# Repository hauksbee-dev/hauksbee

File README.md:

# Hauksbee

**Your design files already contain a running system, with Hauksbee you execute it.**

Hand Hauksbee the artifacts you already produce: the layout, schematic, fab archive, BOM and placement data, fitted variant, compiled firmware, or even the faulty and fixed revisions in a git history. It reconstructs the circuit the copper implements, binds device models, solves it, and boots firmware against the solved board. Findings arrive with the exact evidence that caused them.

A design-rule checker checks geometry against rules. A schematic simulator executes the circuit it was given. Hauksbee's different job is to execute and cross-check the evidence that will become the product: native design files, manufacturing output, assembled-part identity, and firmware.

**New here?** Start with [START_HERE](docs/START_HERE.md). The authoritative scope and backend matrix live in [CAPABILITIES](docs/about/CAPABILITIES.md) and [LIMITATIONS](docs/about/LIMITATIONS.md).

## Get Hauksbee

No binary release is published yet, so build from source. From a checkout of
this repository on macOS/Linux:

```bash
scripts/install-sims.sh --check   # reports which simulator backends are missing
scripts/install.sh
```

`scripts/install.sh` checks the Rust, Bun, clang/libclang, and libsimavr
prerequisites, builds the default shape, and installs `hauksbee`, `hauksbee-ci`,
and `hauksbee-mcp`; external simulators use `scripts/install-sims.sh`. Windows
x64 uses the permissive build documented in
[START_HERE](docs/START_HERE.md#install-and-first-run). Signing, notarisation,
and artifact provenance are release gates; see
[release and licensing](docs/about/release-and-licensing.md).

Once a release is published, the installers below fetch the latest release and
check each asset against the `.sha256` sidecar published beside it. Until then
they exit with an error. Hauksbee is pre-1.0, so you may prefer to pin a tag:
add `-s -- --version vX.Y.Z` after `bash` (PowerShell: download the script and
pass `-Version vX.Y.Z`).

```bash
curl -fsSL https://raw.githubusercontent.com/hauksbee-dev/hauksbee/main/scripts/get-hauksbee.sh | bash
```

Windows (PowerShell):

```powershell
irm https://raw.githubusercontent.com/hauksbee-dev/hauksbee/main/scripts/get-hauksbee.ps1 | iex
```

Once a release exists, `Hauksbee.app` will also be on the
[release page](https://github.com/hauksbee-dev/hauksbee/releases/latest); a
macOS app is published only after its same-source signing and notarisation
gates pass. Ordinary analysis is local. The optional datasheet drafting sends
the datasheet's text to the LLM backend you chose, only after an explicit
consent notice (see
[choosing a backend](docs/models/MODELS.md#choosing-a-backend)); nothing is
ever attached to an issue automatically.

Once the public GHCR package is published, CI images are available as `:slim`
(static checks + AVR co-sim) and `:full` (adds Renode, Espressif QEMU, and
autorouting). Use immutable version/digest references, not floating tags. See
[DOCKER](docs/ci/DOCKER.md).

## Five kinds of evidence, one engine

### Board evidence

Native KiCad, Eagle, Altium, EasyEDA, IPC-2581, ODB++, and schematic-only inputs become one electrical intermediate representation. Static checks, model binding, solver construction, and firmware coupling all consume that same representation rather than separate hand-translated, often idealised diagrams.

### Fab evidence

Gerber, drill, job metadata, and IPC-D-356 can reconstruct what the factory was asked to make. The current closed-loop gate records 99.7–100% native-net partition agreement over located pads across seven routed boards.

### Assembly evidence

BOM, placement, and fitted/no-fit variants participate before model binding. Ambiguous part identity, contradictory dimensions, unknown references, or an assembly that leaves every active component open cannot produce a green simulation. The exact assembly inputs travel with the evidence inventory.

### Firmware evidence

Compiled firmware runs on supported MCU backends whose pins and peripherals couple to the solved circuit. This makes control-state questions executable: the same copper can pass when firmware drives a gate on time and fail when it never does. UART output alone is never promoted into proof that GPIO or an analogue peripheral was exercised.

### Git-history evidence

The development suite converts documented upstream hardware fixes into
hash-pinned parent/fixed regressions. Each pair runs through the same binary
with a declared machine field expected to distinguish it.

Passing this comparison shows that the detector responds differently to the two revisions. It does not, by itself, prove the root cause or demonstrate a full red-to-green board fix.

## Ninety seconds, no board file required

The binaries carry a small board and a real CI spec:

```bash
hauksbee doctor --json
hauksbee run --example blinky --check --plain
hauksbee serve
```

The second command runs every static check on the bundled blinky board and prints a plain-language verdict (`hauksbee check <board>` is shorthand for `hauksbee run --check <board>`). `hauksbee serve` opens the same engine through the local browser UI (the same page the app opens), with sample boards, a checks composer, live 2D copper, probes, and report export. Captured first-run transcripts are retained under [`examples/sessions/`](examples/sessions/).

## Every input an authority

This authority chain matters. If a fab archive contains IPC-D-356, Hauksbee uses that package-authored connectivity instead of guessing nets from copper. If exporter metadata contradicts a filename, the conflict is visible. If a BOM or fitted variant contradicts the nominal layout, analysis refuses before model binding. The same input inventory and causal evidence travels through the human and machine-readable outputs.

The detailed architecture is in [ARCHITECTURE](docs/about/ARCHITECTURE.md).

## Current proof, with the denominator attached

These are source-bound software, simulation, or emulator results. They are not measurements on fabricated hardware.

### Raspberry Pi 4 USB-C faulty/repaired pair

Reproduce with `cargo test -p hauksbee-engine --test usb_c_rpi4 -- --nocapture`. The generic classifier reports the reconstructed faulty topology as `AudioAccessory`/VBUS withheld and the repaired topology as healthy. The files are labelled reconstructions.

### Fab-only connectivity recovery

Run the required-corpus `gerber_closedloop` test documented in [GERBER](docs/ingest/GERBER.md). The seven-board loop currently records 99.7–100% native-net partition agreement over pads that were located. A separate native-Eagle oracle covers 2,208 shared pad centres and 1,236 reconstructed nets with zero false merges. Agreement is conditional on located pads. The Eagle row is one-sided without drill data: missing barrels can still split nets.

### As-built assembly gate

`cargo test -p hauksbee-ci --test assembly_inputs_ci -- --nocapture` runs seven production tests for BOM, placement, fitted/no-fit variant, exact input hashes, and contradiction or empty-assembly refusal.

### Solver performance gate

`cargo test --release -p hauksbee-solve --test speed_gate -- --nocapture`
regenerates and checks the [performance table](docs/about/speed-gate-results.md).
The array row measures disclosed drift, not ngspice agreement. Raw wall time is
host-dependent; use the generated table from the candidate you are evaluating.

### Known-defect regressions

The development suite runs exact parent/fixed revisions through the same
binary and distinguishes full red-to-green results from cases where the target
defect disappears but unrelated failures or missing coverage remain.

## What ships in the engine

### Inputs

- Native KiCad PCB and schematic files, including hierarchy and schematic-only analysis.
- Eagle XML layouts, Altium `.PcbDoc`, EasyEDA Standard `.json` and Pro `.epcb`/`.epro` (connectivity and counted copper; see [`docs/ingest/EASYEDA.md`](docs/ingest/EASYEDA.md)), IPC-D-356, IPC-2581, and ODB++ archives or directories.
- Gerber/drill/fab archives, with X2, `.gbrjob`, Altium LDP/EXTREP metadata, and explicit authority/refusal handling.
- BOM, pick-and-place, and fitted/no-fit variant inputs before model binding.
- Firmware images and project bundles for supported MCU backends.

Pre-Eagle-6 binary layouts and legacy KiCad 5 `.sch` are intentionally refused. Format-specific evidence and limitations live under [`docs/ingest/`](docs/ingest/).

### Checks and analyses

- Copper shorts and clearances, lint, USB-C CC classification, boot straps, internal resource conflicts, I2C loading, device configuration decoding, and DNP policy.
- Trace ampacity, quasi-static controlled-impedance estimates, topology-aware ripple checks, back-power paths, behavioural power ICs, and transient brownout scenarios.
- Small-signal AC analysis with gain/phase assertions and a steady-state, per-device thermal estimator.
- Typed model coverage and import diagnostics: recovered, partial, unplaced, refused, confidence basis, parser stage, and next action.

Hauksbee's SI checks are closed-form estimates, not a 3D field solver. Thermal analysis estimates junction temperature per device, not a board thermal field. AC analysis is linearised about the operating point. Those boundaries are part of the output, not footnotes added later.

## When a part has no model

An unresolved active part is not the end of the workflow. Hauksbee names the reference, connected nets, identity evidence, winning model layer, and the stronger analyses that remain invalid. It binds the part open rather than inventing plausible behaviour.

The model workflow is data-driven and does not require recompiling Hauksbee:

```bash
hauksbee models coverage board.kicad_pcb --json
hauksbee models prepare board.kicad_pcb --pack-dir model-packs/my-board
# prints the unresolved active-device inventory and asks [y/N] before writing
hauksbee models new U3 --board board.kicad_pcb \
  --kind vreg --out models/u3.toml
hauksbee models lint models/u3.toml
hauksbee run board.kicad_pcb --models-dir models --report --plain
```

`models prepare` is local and approval-gated: it inventories the connected active devices, shows the exact pack paths it would create, defaults to no, and does not fetch a datasheet, call an LLM, or install a pack. `models new` starts from one board identity and refuses to guess the IC's behaviour. `models lint` applies the same schema and behavioural validation used by binding. `hauksbee models resolve board.kicad_pcb` then shows which source and layer won; the full report shows whether the declared pin roles actually connected. Model packs can be installed, listed, overridden, and removed without editing the built-in database.

**What datasheet drafting costs.** Drafting runs once per part and the saved card is reused on every later board. On a ChatGPT Plus plan signed in to `codex`, we measured one public board (Glasgow revD1, 10 of its 17 unmodelled active parts, high effort, including retries and two parts that still failed validation). With `gpt-6-luna` each part took about 1% of the 5-hour limit and about 0.1% of the weekly limit, so the ten used roughly 8% of one 5-hour window and 1% of the week. With `gpt-6.1-sol`, the default, four of the same parts took about 6% of the 5-hour limit and about 1% of the weekly limit each, around 13 times as much; at that rate all 17 parts would use about a full 5-hour window. With an API key you pay per token instead: at list price that was about $0.50 for the ten Luna parts and about $0.50 per part on Sol. This is one board and one run read from integer percentages, and plan limits change, so treat the figures as an order of magnitude.

The report separates the stages: a device can be extracted from CAD, matched to an exact identity/pin map, carry safe static contracts, and still lack the executable behaviour needed by analog or firmware simulation. `critical_parts_bound` is the last of those stages (executable behavioural-model coverage), not a claim that the other critical parts failed to parse.

The browser is the primary, easier workbench for the same flow. Open `hauksbee serve`, drop a board, expand **Model coverage**, and click a part to see its exact winning model, source, pins/nets, implemented behavior, and declared omissions. **Extend model** makes a local read-only draft; Check uses the engine validator; Save is a separate reviewed write and refuses overwrite. No LLM is involved unless the user separately chooses the consent-gated datasheet-draft action.

Clicking copper is equally direct: watch the trace live, add a voltage, rail, toggle, or boot assertion, or attach a waveform, pushbutton, or toggle. A live attachment stamps a real source/contact into the solver and queues the same ID into ordinary replayable `[[peripheral]]` TOML. Hauksbee never turns a net into a control merely because it is named `A0` or `INPUT`; the engine must declare a source or the user must attach one explicitly. See [Capabilities](docs/about/CAPABILITIES.md) for the supported browser, CLI, MCP, approval, and board-analysis surfaces.

Clicked I²C/SPI parts have the same treatment. Pick or paste a local register-map spec (or choose a checked-in behavior subset from the browser's bundled local catalog), set physical inputs, and attach those exact bytes to the running bus; the browser retains the identical self-contained `[[sensor]]` entry for replay. Once that behavior is stored in an exact model card it auto-attaches on future boards. Model cards can require bus-mode straps and derive a selectable I²C address from exact board supply/ground ties. Bad spec bytes, typoed inputs, ambiguous straps, unknown CS nets, and duplicate ids refuse instead of falling back to plausible zeros.

## Firmware against solved copper

The engine couples MCU pins and peripherals to the solved board. Current backends include AVR/libsimavr, Renode platforms for selected STM32, RP2040, nRF52 and RISC-V paths, and Espressif QEMU for the ESP32 family. GPIO, UART, ADC, I2C, SPI, timing, and peripheral coverage varies by chip and backend; [MCU.md](docs/cosim/MCU.md) states each proven row and each unsupported path.

UART boot is not promoted to a GPIO claim. A mailbox-backed peripheral is not promoted to native register observation. A simulator-only result is not promoted to hardware validation.

## Reproducibility

For an analysis run, emit an immutable manifest:

```bash
hauksbee run board.kicad_pcb --check --json \
  --emit-manifest evidence/run.manifest.json
hauksbee reproduce evidence/run.manifest.json
```

The manifest binds input bytes, directories, model sources, tool/build revisions, simulator selection, options, and environment selectors. Numeric results also carry a typed error budget: solver tolerances, residual status, invalid windows, timing quantisation, and model uncertainty where available. See [RUN_MANIFESTS](docs/analysis/RUN_MANIFESTS.md) and [ERROR_BUDGETS](docs/analysis/ERROR_BUDGETS.md).

## Gate it, if you gate things

CI is one consumer of the engine rather than its definition. Specs can assert voltage, toggles, boot coverage, rail windows, faults, temperature, protection trips, peripherals, model coverage, AC gain or phase margin, and hardware-trace features, with scenarios and fuzzed initial states. The exact schema and runnable examples are in [CI](docs/ci/CI.md) and [EXAMPLES](docs/ci/EXAMPLES.md).

This is the shipped `crates/hauksbee-ci/examples/boot_gate_pass.toml`. Its
`board` and `firmware` paths are relative to the spec file, not to the directory
you run from:

```toml
name = "boot_coverage: MOSFET gate driven promptly"
board = "boards/boot_gate.kicad_pcb"
firmware = "../../../testdata/firmware/boot_gate_a/boot_gate.hex"
mcu = "atmega328p"   # informational; the core comes from the board
duration_ms = 50

[[supply]]
net = "+5V"
kind = "ideal"
volts = 5.0

[[assert]]
kind = "boot_coverage"
net = "GATE_CTRL"
min = 3.0
deadline_ms = 20.0

[[assert]]
kind = "no_faults"
```

From a checkout of this repository (a spec of your own works the same way):

```bash
hauksbee-ci check crates/hauksbee-ci/examples/boot_gate_pass.toml
hauksbee-ci run crates/hauksbee-ci/examples/boot_gate_pass.toml --json --junit out.xml
```

`hauksbee-ci run --example blinky` runs a bundled spec without a checkout.

### Fits into an existing repository

```bash
hauksbee-ci init my_board.kicad_pcb
hauksbee-ci hook install
hauksbee-ci github-action
hauksbee watch my_board.kicad_pcb
```

Integration surfaces include:

- a GitHub Action and generated workflow;
- pre-commit hooks that cover native boards, fab archives, IPC-2581 XML, and root or nested `ci/*.toml` specs;
- a KiCad plugin;
- a VS Code extension with schema completion, diagnostics, run/check commands, and loader-parity tests;
- JSON, JUnit, SARIF/GitHub annotations, self-contained HTML reports, and a stdio MCP server for agents.

```bash
claude mcp add --transport stdio hauksbee -- hauksbee-mcp
```

## Verdicts are evidence states

For `hauksbee run`:

- **0**: clean, or report-only output without `--strict`.
- **1**: the input was not analysed (missing, unreadable, unsupported, or an LFS pointer).
- **2**: gate-grade findings under `--strict`, or invalid CLI usage.
- **3**: the request was understood, but a trustworthy answer could not be produced. The output names the declined claim, missing prerequisite, valid partial result, and next action.

For `hauksbee-ci run`:

- **0**: all assertions held and the run was valid.
- **1**: an assertion failed.
- **2**: the spec or board input was invalid.
- **3**: the analysis result was not trustworthy enough to grade.

Evidence labels should be read literally:

- **Source-bound static result:** derived from the identified design bytes and documented rules or models.
- **Simulation/emulator result:** observed in the identified solver or backend, with its coverage limits.
- **Analytical oracle:** an independently calculated reference used for cross-checking.
- **Hardware trace:** measured only when the trace says `provenance = "real"`; current bundled trace fixtures are synthetic.
- **Invalid/unassessed:** required evidence is missing. Never a negative finding and never green.

Hauksbee is a pre-fab evidence engine, not a substitute for design review, vendor limits, KiCad/Altium DRC, signal-integrity field simulation, compliance testing, or the bench.

## Repository map

- `crates/hauksbee-extract`: CAD, fab, schematic, BOM, and placement ingestion.
- `crates/hauksbee-models`: device and MCU model resolution.
- `crates/hauksbee-ir`: circuit intermediate representation and evidence types.
- `crates/hauksbee-solve`: linear, nonlinear, transient, and AC solvers.
- `crates/hauksbee-mcu`: MCU backends and circuit coupling.
- `crates/hauksbee-engine`: CLI and end-to-end analysis pipeline.
- `crates/hauksbee-ci`: CI spec loader, assertions, reports, and integrations.
- `crates/hauksbee-server`, `frontend/`: local web front door and live board UI.
- `crates/hauksbee-mcp`: structured agent tools over stdio.
- `qc/`: unseen-board sampling and value-grading scripts.

The KiCad parser/producer layer is vendored under [`vendor/kicad-forge`](vendor/kicad-forge); provenance and update rules are in [VENDORED](vendor/kicad-forge/VENDORED.md).

## Origin, licence, and acknowledgements

Hauksbee grew out of the need to validate a large private analogue board whose bespoke emulator could only execute the intended circuit. The private board is not redistributed here, and private-suite evidence is not presented as a publicly rerunnable result. However, the emulator was able to diagnose several major failures on the board, and has been exceedingly useful in pursuing that project. [PRIVATE_SUITE](docs/about/PRIVATE_SUITE.md) records that boundary.

Hauksbee source is Apache-2.0; retain [NOTICE](NOTICE) when redistributing it. The optional in-process AVR backend links GPL-3.0 libsimavr, so a binary built with that feature is GPL-3.0. Builds without AVR use Renode and Espressif QEMU as separate processes and retain the permissive Hauksbee licence. Artifact-by- artifact obligations are in [COMPLIANCE](COMPLIANCE.md).

Major upstream systems include [KiCad](https://www.kicad.org), [ngspice](https://ngspice.sourceforge.io), [simavr](https://github.com/buserror/simavr), [Renode](https://renode.io), and [Espressif QEMU](https://github.com/espressif/qemu). See the relevant ingest, solver, co-simulation, and licensing docs for exact provenance.

Contributing and test requirements are in [CONTRIBUTING](CONTRIBUTING.md). Security reports follow [SECURITY](SECURITY.md).

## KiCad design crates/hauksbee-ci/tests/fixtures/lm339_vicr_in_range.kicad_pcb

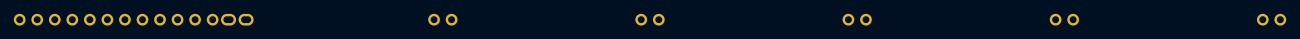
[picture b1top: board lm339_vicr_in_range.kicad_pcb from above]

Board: 2 copper layers, 7 parts (0 on the bottom side), 5 nets, no tracks yet.

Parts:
CBYP: 100nF; C_0805_2012Metric
R1: 62k; R_0805_2012Metric
R2, R3, R4, R5: 10k; R_0805_2012Metric
U1: LM339B; DIP-14_W7.62mm

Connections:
GND: CBYP.2, R2.2, R4.2, U1.6, U1.7, U1.8, U1.9, U1.10, U1.11, U1.12
INM: R3.2, R4.1, U1.4
INP: R1.2, R2.1, U1.5
OUT: R5.1, U1.2
V5: CBYP.1, R1.1, R3.1, R5.2, U1.3

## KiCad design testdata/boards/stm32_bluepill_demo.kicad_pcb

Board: 0 copper layers, 4 parts (0 on the bottom side), 5 nets, no tracks yet.

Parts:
D1: RED_LED; LED_D5.0mm
R1: 330; R_Axial_DIN0207_L6.3mm_D2.5mm
R2: 4k7; R_Axial_DIN0207_L6.3mm_D2.5mm
U1: STM32F103C8T6; LQFP-48_7x7mm_P0.5mm

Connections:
+3V3: U1.9, U1.24, U1.36, U1.48
GND: D1.K, R2.2, U1.8, U1.23, U1.35, U1.44
LED_A: D1.A, R1.2
PA5_OUT: R1.1, U1.15
PC13_LED: R2.1, U1.2

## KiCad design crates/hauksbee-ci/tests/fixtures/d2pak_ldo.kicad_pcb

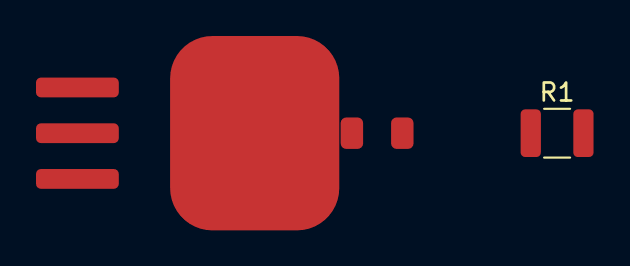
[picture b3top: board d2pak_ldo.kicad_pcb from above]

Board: 2 copper layers, 3 parts (0 on the bottom side), 2 nets, no tracks yet.

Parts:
C1: 10uF; C_1206_3216Metric
R1: 33; R_1210_3225Metric
U1: LD1086D2T33TR; TO-263-3_TabPin2

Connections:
GND: C1.2, R1.2, U1.1
VOUT: C1.1, R1.1, U1.2

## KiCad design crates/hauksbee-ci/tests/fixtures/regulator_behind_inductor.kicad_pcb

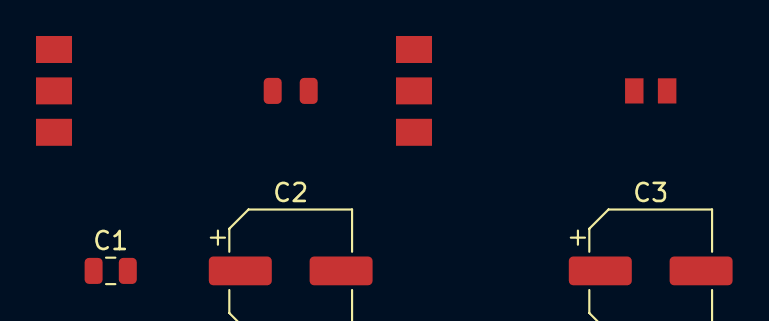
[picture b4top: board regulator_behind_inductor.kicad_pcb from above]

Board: 2 copper layers, 7 parts (0 on the bottom side), 5 nets, no tracks yet.

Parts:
C1: 10uF; C_0805_2012Metric
C2, C3: 22uF; CP_Elec_6.3x5.4
L1: 10uH; L_0805_2012Metric
R1: 330; R_0805_2012Metric
U1: AMS1117-5.0; SOT-223-3_TabPin2
U2: AMS1117-3.3; SOT-223-3_TabPin2

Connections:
+3V3: C3.1, R1.1, U2.2
+5V: L1.2, U2.3
GND: C1.2, C2.2, C3.2, R1.2, U1.1, U2.1
SW: C2.1, L1.1, U1.2
VIN: C1.1, U1.3

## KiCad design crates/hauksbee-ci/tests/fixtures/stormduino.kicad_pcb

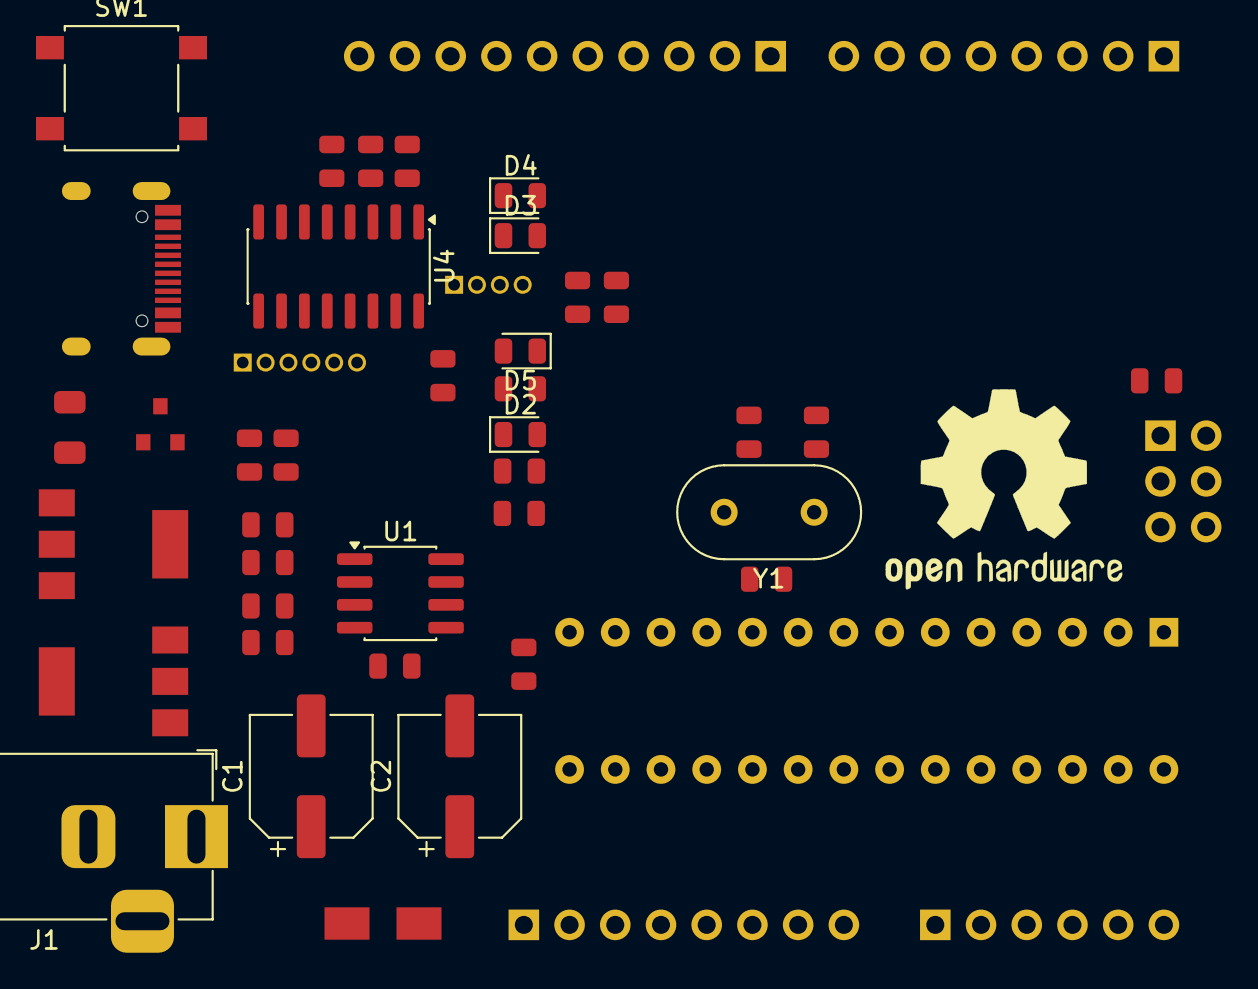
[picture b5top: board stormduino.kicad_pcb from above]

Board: 2 copper layers, 46 parts (0 on the bottom side), 49 nets, no tracks yet.

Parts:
C1: 47uF; CP_Elec_6.3x5.4
C2, C6: 10uF; C_0805_2012Metric
C2#2: 10uF; CP_Elec_6.3x5.4
C3, C4, C7, C9, C10, C13: 100nF; C_0805_2012Metric
C8: 100nf; C_0805_2012Metric
C11, C12: 22pF; C_0805_2012Metric
D1: DIODE; D_SMA
D2, D3, D4, D5: LED; LED_0805_2012Metric
F1: Fuse; C_1206_3216Metric
J1: Jack-DC; BarrelJack_Horizontal
J2: USB_C_Receptacle_USB2.0; USB_C_Receptacle_HRO_TYPE-C-31-M-12
J3: Conn_02x03_Odd_Even; PinHeader_2x03_P2.54mm_Vertical
J4: Conn_01x06_MountingPin; PinHeader_1x06_P2.54mm_Vertical
J5, J7: Conn_01x08_MountingPin; PinHeader_1x08_P2.54mm_Vertical
J6: Conn_01x10_MountingPin; PinHeader_1x10_P2.54mm_Vertical
J8: Conn_01x04_MountingPin; PinHeader_1x04_P1.27mm_Vertical
J9: Conn_01x06_MountingPin; PinHeader_1x06_P1.27mm_Vertical
Q1: BS250; SOT-23
R1, R2: 10k; C_0805_2012Metric
R3, R4, R5, R6, R7, R8: 1k; C_0805_2012Metric
R9: 1K; C_0805_2012Metric
R10: 1M; C_0805_2012Metric
SW1: SW_Push; SW_SPST_B3S-1000
U1: LM358; SOP-8_3.76x4.96mm_P1.27mm
U2: AMS1117-5.0; SOT-223-3_TabPin2
U3: AMS1117-3.3; SOT-223-3_TabPin2
U4: CH340C; SOIC-16_3.9x9.9mm_P1.27mm
U5: ATmega328P-PU; DIP-28_W7.62mm
Y1: 16 Mhz; Resonator-2Pin_W10.0mm_H5.0mm

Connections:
+3V3: C3.2, C6.1, C9.1, J5.4, U1.2, U3.2, U4.4
+5V: C2.1, C2#2.1, C4.1, C7.1, C10.1, J3.2, J5.2, J5.5, Q1.2, R6.2, R7.1, R8.1, R9.2, U1.8, U2.2, U3.3, U5.7, U5.20
/A0: J4.1, U5.23
/A1: J4.2, U5.24
/A2: J4.3, U5.25
/A3: J4.4, U5.26
/A4: J4.5, J6.9, U5.27
/A5: J4.6, J6.10, U5.28
/AREF: C13.1, J6.8, U5.21
/CTS: J9.1, U4.9
/D0: D4.1, J7.1, J8.4, R3.1, U5.2
/D1: D3.1, J7.2, J8.3, R4.1, U5.3
/D2: J7.3, U5.4
/D3: J7.4, U5.5
/D4: J7.5, U5.6
/D5: J7.6, U5.11
/D6: J7.7, U5.12
/D7: J7.8, U5.13
/D8: J6.1, U5.14
/D9: J6.2, U5.15
/D10: J6.3, U5.16
/D11: J3.4, J6.4, U5.17
/D12: J3.1, J6.5, U5.18
/D13: J3.3, J6.6, U1.5, U5.19
/DCD: J9.4, U4.12
/DSR: J9.2, U4.10
/DTR: C8.1, J3.5, J5.3, R9.1, SW1.2, U5.1
/R232: J9.6, U4.15
/RI: J9.3, U4.11
/RTS: J9.5, U4.14
/VBUS: F1.1, J8.1, Q1.3, U4.16
/VIN: C1.1, D1.2, J5.8, R1.1, U2.3
GND: C1.2, C2.2, C2#2.2, C3.1, C4.2, C6.2, C7.2, C9.2, C10.2, C11.1, C12.2, C13.2, D2.1, D5.1, J1.2, J2.A1, J2.A12, J2.B1, J2.B12, J3.6, J5.6, J5.7, J6.7, J8.2, R2.2, SW1.1, U1.4, U2.1, U3.1, U4.1, U5.8, U5.22
unnamed: C8.2, U4.13
unnamed: C11.2, R10.1, U5.9, Y1.1
unnamed: C12.1, R10.2, U5.10, Y1.2
unnamed: D1.1, J1.1
unnamed: D2.2, R5.2
unnamed: D3.2, R6.1
unnamed: D4.2, R7.2
unnamed: D5.2, R8.2
unnamed: F1.2, J2.A4, J2.A9, J2.B4, J2.B9
unnamed: J2.A6, J2.B6, U4.5
unnamed: J2.A7, J2.B7, U4.6
unnamed: Q1.1, U1.1
unnamed: R1.2, R2.1, U1.3
unnamed: R3.2, U4.2
unnamed: R4.2, U4.3
unnamed: R5.1, U1.6, U1.7

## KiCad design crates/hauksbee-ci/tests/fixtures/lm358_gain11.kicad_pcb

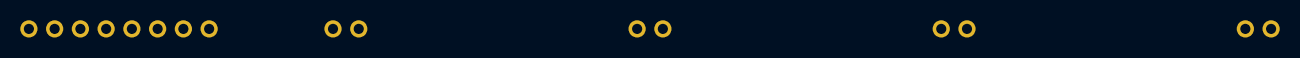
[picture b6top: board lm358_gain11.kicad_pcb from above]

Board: 2 copper layers, 5 parts (0 on the bottom side), 4 nets, no tracks yet.

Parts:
CBYP: 100nF; C_0805_2012Metric
RF: 10k; R_0805_2012Metric
RG: 1k; R_0805_2012Metric
RL: 2k; R_0805_2012Metric
U1: LM358; DIP-8_W7.62mm

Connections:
GND: CBYP.2, RG.2, RL.2, U1.4, U1.5, U1.6
INM: RF.2, RG.1, U1.2
OUT: RF.1, RL.1, U1.1
V5: CBYP.1, U1.8

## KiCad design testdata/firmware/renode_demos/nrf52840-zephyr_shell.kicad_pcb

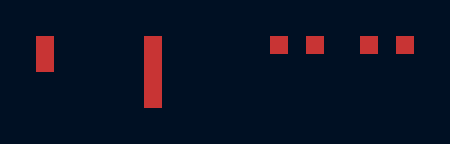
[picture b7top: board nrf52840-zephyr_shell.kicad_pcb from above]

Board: 2 copper layers, 3 parts (0 on the bottom side), 2 nets, no tracks yet.

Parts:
D1: RED_LED; LED_0805_2012Metric
R1: 330; R_0805_2012Metric
U1: nRF52840; AQFN-73_9x9mm_P0.5mm

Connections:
GND: D1.K, R1.2, U1.1
LED_A: D1.A, R1.1, U1.3

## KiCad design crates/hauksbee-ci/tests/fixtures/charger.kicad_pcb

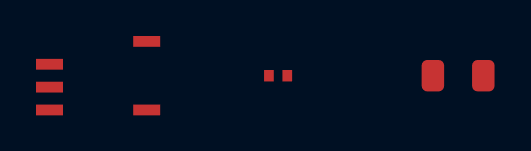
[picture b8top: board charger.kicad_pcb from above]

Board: 2 copper layers, 3 parts (0 on the bottom side), 4 nets, no tracks yet.

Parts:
C1: 10uF; C_1206_3216Metric
R1: 5k; R_0402_1005Metric
U1: TP4056; SOIC-8_3.9x4.9mm_P1.27mm

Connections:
GND: C1.2, R1.2, U1.3
PROG: R1.1, U1.2
VBAT: C1.1, U1.5
VIN: U1.4, U1.8
